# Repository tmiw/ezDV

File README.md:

# ezDV

This repository contains both the hardware and firmware for a portable battery-powered device that can
(de)modulate [FreeDV](https://freedv.org/) from an attached radio. The board is centered around the 
following components:

* [Espressif ESP32-S3](https://www.espressif.com/sites/default/files/documentation/esp32-s3_datasheet_en.pdf)
* [TLV320 digital audio codec chip](https://www.ti.com/cn/lit/ds/symlink/tlv320aic3254.pdf?ts=1651153824042) produced by Texas Instruments ([application notes](https://www.ti.com/lit/an/slaa408a/slaa408a.pdf?ts=1651208477772&ref_url=https%253A%252F%252Fwww.google.com%252F)).

## User's guide

See [here](https://tmiw.github.io/ezDV/) for the latest copy of the user manual for ezDV, which describes its
general use and operation.

## Building the firmware

Install [ESP-IDF v5.3](https://docs.espressif.com/projects/esp-idf/en/v5.3/esp32s3/get-started/index.html) and then run the following:

```
. /path/to/esp-idf/export.sh
git submodule update --init --checkout --recursive
cd firmware
idf.py build
```
## Flashing the firmware

### Using ESP-IDF

Turn on ezDV (see below) and plug it into your computer's USB port, then run the following:

```
idf.py -p /dev/ttyxxx0 flash monitor
```

Where `/dev/ttyxxx0` (or `COMx:` on Windows) is the serial port created by your operating system after plugging ezDV in.

### Using ESP Flash Tool

On Windows, you can use the ESP Flash Tool to flash ezDV. This does not require installation of ESP-IDF.

1. Download the ESP Flash Tool from https://www.espressif.com/en/support/download/other-tools.
2. Decompress all of the files in the ZIP file and execute flash\_download\_tool\_3.9.3.exe.
3. Select "ESP32-S3" for "ChipType", "Develop" for "WorkMode" and "USB" for "LoadMode" as shown below:

4. Add rows for each of the .bin files in the resulting screen:

| File Name | Offset |
|---|---|
| bootloader.bin | 0x0 |
| partition-table.bin | 0x8000 |
| ota\_data\_initial.bin | 0xF000 |
| ezdv.bin | 0x20000 |
| http_0.bin | 0x7F8000 |
| q8_models.bin | 0xAE6000 |

Additionally, check each of the checkboxes to the left of the file name. It should look something like this, with each of the rows having a green background:

5. Set "SPI SPEED" to "80 MHz" and "SPI MODE" to "DIO".

6. Plug ezDV into your computer using a USB-C cable and turn it on by holding down the Mode button for a few seconds. Device Manager should show a new COM port named "USB/JTAG serial debug unit" or similar. Enter this COM port into the "COM" field in the application.

7. (Optional) Push the ERASE button. This will show a green "SYNC" indicator for a bit followed by "Download" and then "FINISH" as per the above screenshot. *Note: There will be no firmware installed on the board once this step finishes. You will need to reconfigure ezDV after new firmware has been flashed.*

8. Push the START button. This will go through the same indicators as step 1 but this time will also have a progress bar indicating how far it's gotten in flashing the new software. 

9. Push the STOP button and then close the application. Open the ezDV enclosure and briefly push/release the "Reset" button on the right hand side of the board. If everything went well, you'll see the four LEDs light up for a few seconds indicating that ezDV is booting normally.

### Using esptool

You can also use [esptool](https://github.com/espressif/esptool). From the folder you decompressed the "-full.tar.gz" file into, run:

```
esptool.py --chip esp32s3 -p /dev/cu.usbmodem14101 -b 460800 --before=default_reset --after=hard_reset write_flash --flash_mode dio --flash_freq 80m --flash_size detect 0x0 bootloader.bin 0x20000 ezdv.bin 0x8000 partition-table.bin 0xf000 ota_data_initial.bin 0x7f8000 http_0.bin 0xae6000 q8_models.bin
```

### Flashing test firmware

Firmware that hasn't been released yet (for example, from a pull request that needs testing) is built automatically
for every change made to ezDV's source code. To download it:

1. Sign in to GitHub. (Downloads of test firmware are only available to signed-in users.)
2. Go to the [project's Actions page](https://github.com/tmiw/ezDV/actions/workflows/build_ezdv.yml) and select the
   most recent run for the branch you've been asked to test. For a pull request, you can also select the "Build ezDV"
   check at the bottom of the pull request's page and then "Summary".
3. Scroll down to "Artifacts" and download the file named after that branch and commit (for example,
   "ezdv-rade-v2-d8d0042"). This is a ZIP file containing two files ending in "-full.tar.gz" and "-ota.tar.gz".
4. Decompress the "-full.tar.gz" file into a new folder. On Windows, you can do this using 7-Zip or by running
   `tar xzf filename-full.tar.gz` from a Command Prompt.
5. Flash the resulting .bin files using the ESP Flash Tool or esptool as described above.

*Note: Firmware with RADE V2 support adds a "models" area to ezDV's internal memory that holds RADE V2's neural
network. The first time you install it, you must flash all of the files in the "-full.tar.gz" file over USB
as described above. Afterwards, newer test firmware can be installed using the "-ota.tar.gz" file and the web
interface as long as RADE V2's neural network hasn't changed since you last flashed over USB. If in doubt,
flash the "-full.tar.gz" file over USB. Test firmware is not guaranteed to work, so make sure you
can flash ezDV over USB before trying it.*

*To go back to a released version of the firmware, flash that version's "-full.tar.gz" file over USB.*

### Recovering from a bad flash

If the flash process fails (or you are flashing for the first time), you can manually place ezDV into flash mode by holding down the "GPIO0/Flash" button while pushing the "Reset" button on the board. Hold "GPIO0/Flash" for a second or so after releasing Reset, then release. You can then use ESP-IDF, the ESP Flash Tool or esptool to flash ezDV with working firmware.

## Contributing to ezDV

Pleae read the [Theory of Operation](https://github.com/tmiw/ezDV/blob/main/THEORY_OF_OPERATIONS.md) document for more information about the general hardware and software architecture, along with information about how to contribute changes to ezDV.

## License

This project is subject to the terms of the [TAPR Open Hardware License v1.0](https://tapr.org/the-tapr-open-hardware-license/) (schematics, 
other hardware documentation) and [GNU General Public License v3.0](https://www.gnu.org/licenses/gpl-3.0.en.html) (firmware).

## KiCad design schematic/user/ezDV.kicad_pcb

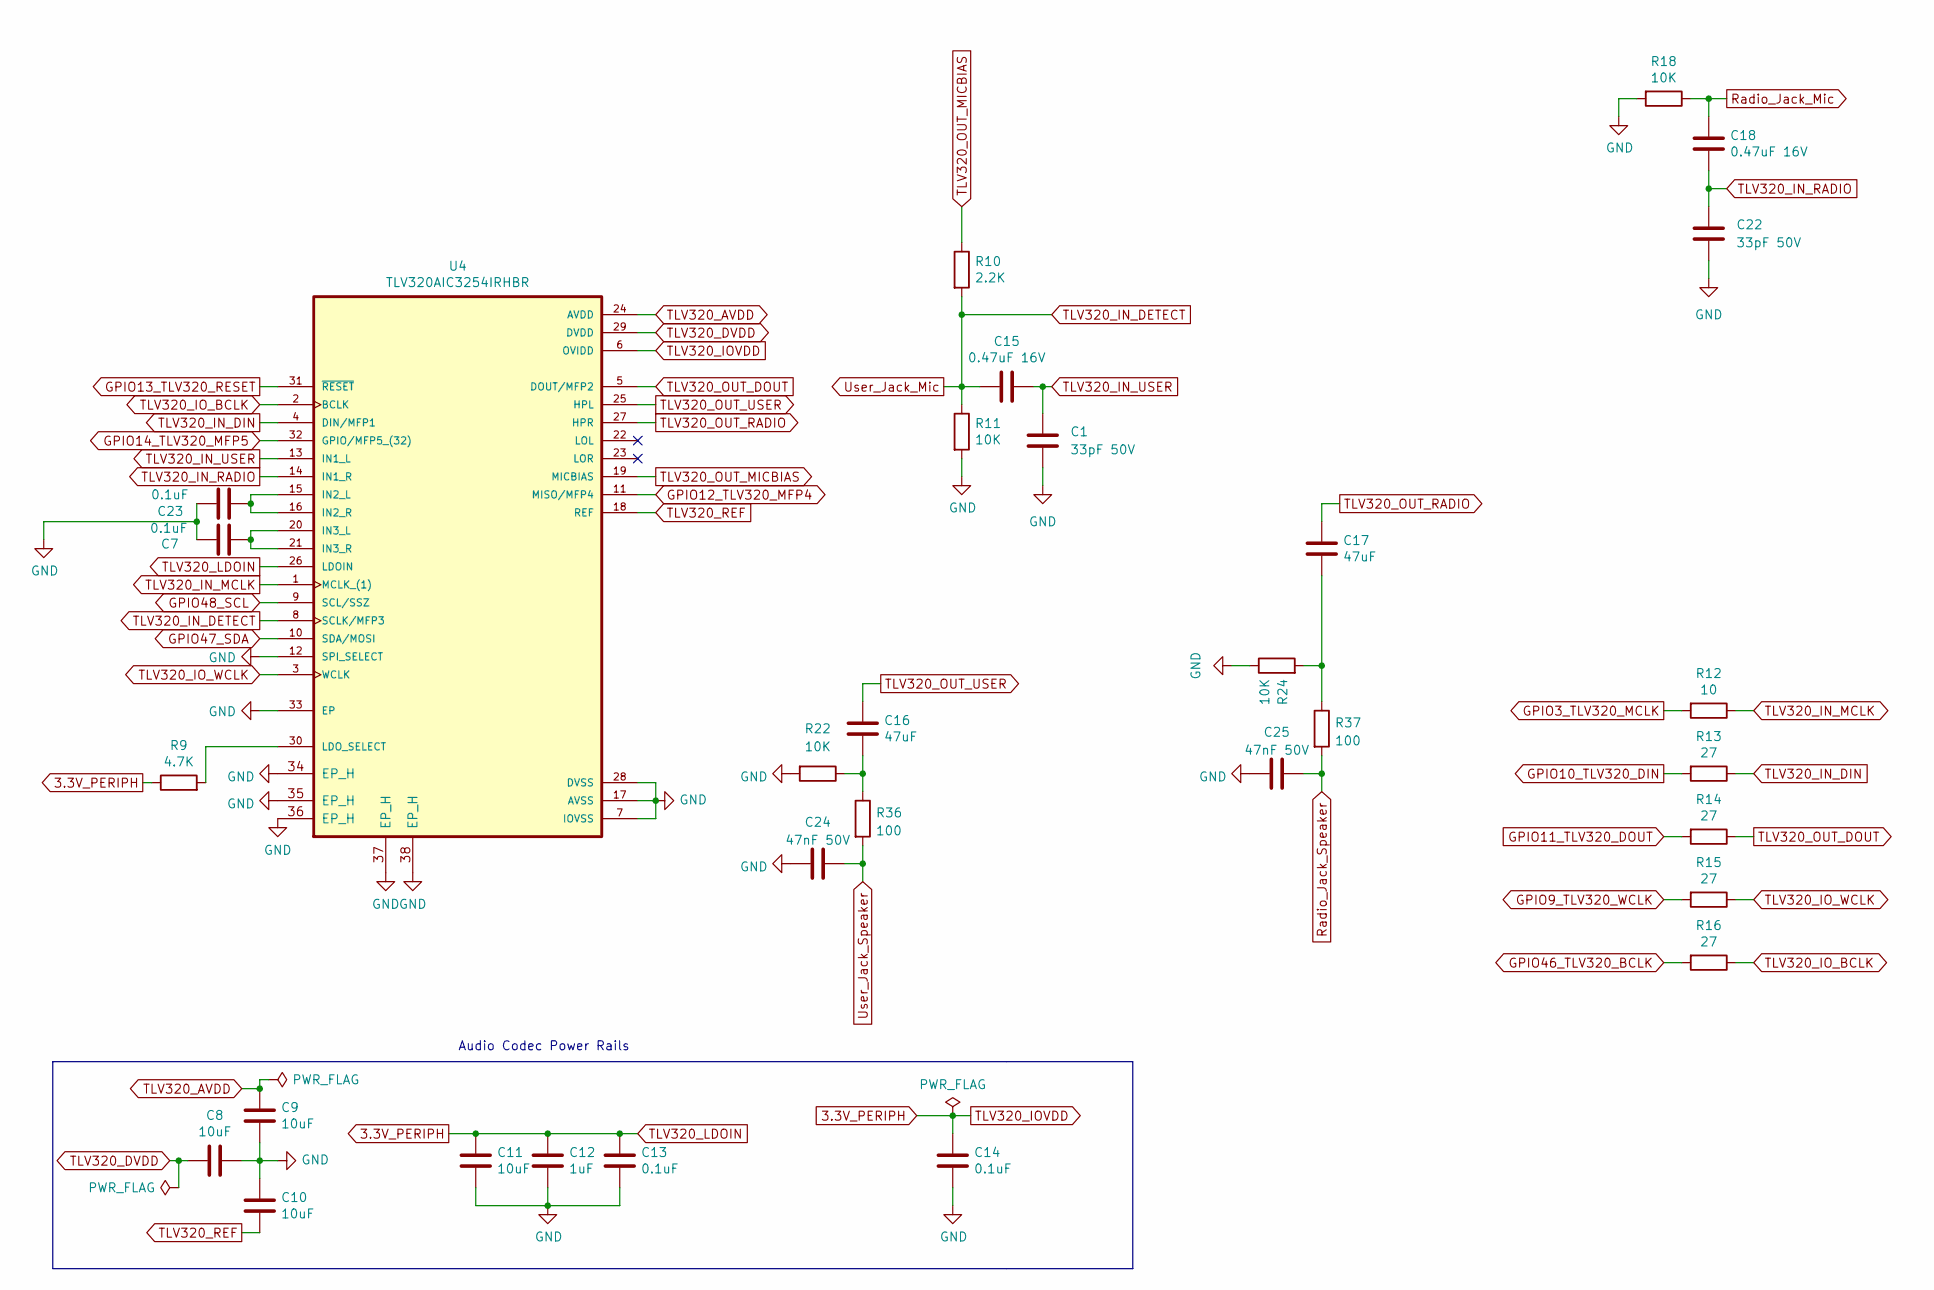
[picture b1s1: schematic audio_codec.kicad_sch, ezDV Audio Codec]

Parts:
C1, C22: 33pF 50V; C_0402_1005Metric; LCSC C1562
C7, C13, C14, C23: 0.1uF; C_0402_1005Metric; LCSC C1525
C8, C9, C10, C11: 10uF; C_0402_1005Metric; LCSC C315248
C12: 1uF; C_0402_1005Metric; LCSC C14445
C15, C18: 0.47uF 16V; C_0402_1005Metric; LCSC C575468
C16, C17: 47uF; C_0603_1608Metric; LCSC C140782
C24, C25: 47nF 50V; C_0402_1005Metric; LCSC C697422
R9: 4.7K; R_0402_1005Metric; LCSC C25900
R10: 2.2K; R_0402_1005Metric; LCSC C114762
R11, R18, R22, R24: 10K; R_0402_1005Metric; LCSC C25744
R12: 10; R_0402_1005Metric; LCSC C25077
R13, R14, R15, R16: 27; R_0402_1005Metric; LCSC C31439
R36, R37: 100; R_0402_1005Metric; LCSC C25076
U4: TLV320AIC3254IRHBR; IC_ADS125H01IRHBT; LCSC C9925

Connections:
3.3V_PERIPH: C11.1, C12.1, C13.1, C14.1, R9.1, U4.6 (OVIDD), U4.26 (LDOIN); also elsewhere on the board
GND: C1.2, C7.2, C8.1, C9.2, C10.1, C11.2, C12.2, C13.2, C14.2, C22.2, C23.2, C24.1, C25.1, R11.2, R18.2, R22.2, R24.1, U4.7 (IOVSS), U4.12 (SPI_SELECT), U4.17 (AVSS), U4.28 (DVSS), U4.33 (EP), U4.34 (EP_H), U4.35 (EP_H), U4.36 (EP_H), U4.37 (EP_H), U4.38 (EP_H); also elsewhere on the board
GPIO3_TLV320_MCLK: R12.2; also elsewhere on the board
GPIO9_TLV320_WCLK: R15.2; also elsewhere on the board
GPIO10_TLV320_DIN: R13.2; also elsewhere on the board
GPIO11_TLV320_DOUT: R14.2; also elsewhere on the board
GPIO12_TLV320_MFP4: U4.11 (MISO/MFP4); also elsewhere on the board
GPIO13_TLV320_RESET: U4.31 (~RESET); also elsewhere on the board
GPIO14_TLV320_MFP5: U4.32 (GPIO/MFP5_(32)); also elsewhere on the board
GPIO46_TLV320_BCLK: R16.2; also elsewhere on the board
GPIO47_SDA: U4.10 (SDA/MOSI); also elsewhere on the board
GPIO48_SCL: U4.9 (SCL/SSZ); also elsewhere on the board
unnamed: C7.1, U4.15 (IN2_L), U4.16 (IN2_R)
unnamed: C16.2, R22.1, R36.1
unnamed: C17.2, R24.2, R37.1
unnamed: C23.1, U4.20 (IN3_L), U4.21 (IN3_R)
unnamed: R9.2, U4.30 (LDO_SELECT)
Radio_Jack_Mic: C18.1, R18.1; also elsewhere on the board
Radio_Jack_Speaker: C25.2, R37.2; also elsewhere on the board
TLV320_AVDD: C9.1, U4.24 (AVDD)
TLV320_DVDD: C8.2, U4.29 (DVDD)
TLV320_IN_DETECT: C15.1, R10.2, R11.1, U4.8 (SCLK/MFP3); also elsewhere on the board
TLV320_IN_DIN: R13.1, U4.4 (DIN/MFP1)
TLV320_IN_MCLK: R12.1, U4.1 (MCLK_(1))
TLV320_IN_RADIO: C18.2, C22.1, U4.14 (IN1_R)
TLV320_IN_USER: C1.1, C15.2, U4.13 (IN1_L)
TLV320_IO_BCLK: R16.1, U4.2 (BCLK)
TLV320_IO_WCLK: R15.1, U4.3 (WCLK)
TLV320_OUT_DOUT: R14.1, U4.5 (DOUT/MFP2)
TLV320_OUT_MICBIAS: R10.1, U4.19 (MICBIAS)
TLV320_OUT_RADIO: C17.1, U4.27 (HPR)
TLV320_OUT_USER: C16.1, U4.25 (HPL)
TLV320_REF: C10.2, U4.18 (REF)
User_Jack_Speaker: C24.2, R36.2; also elsewhere on the board

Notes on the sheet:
Audio Codec Power Rails

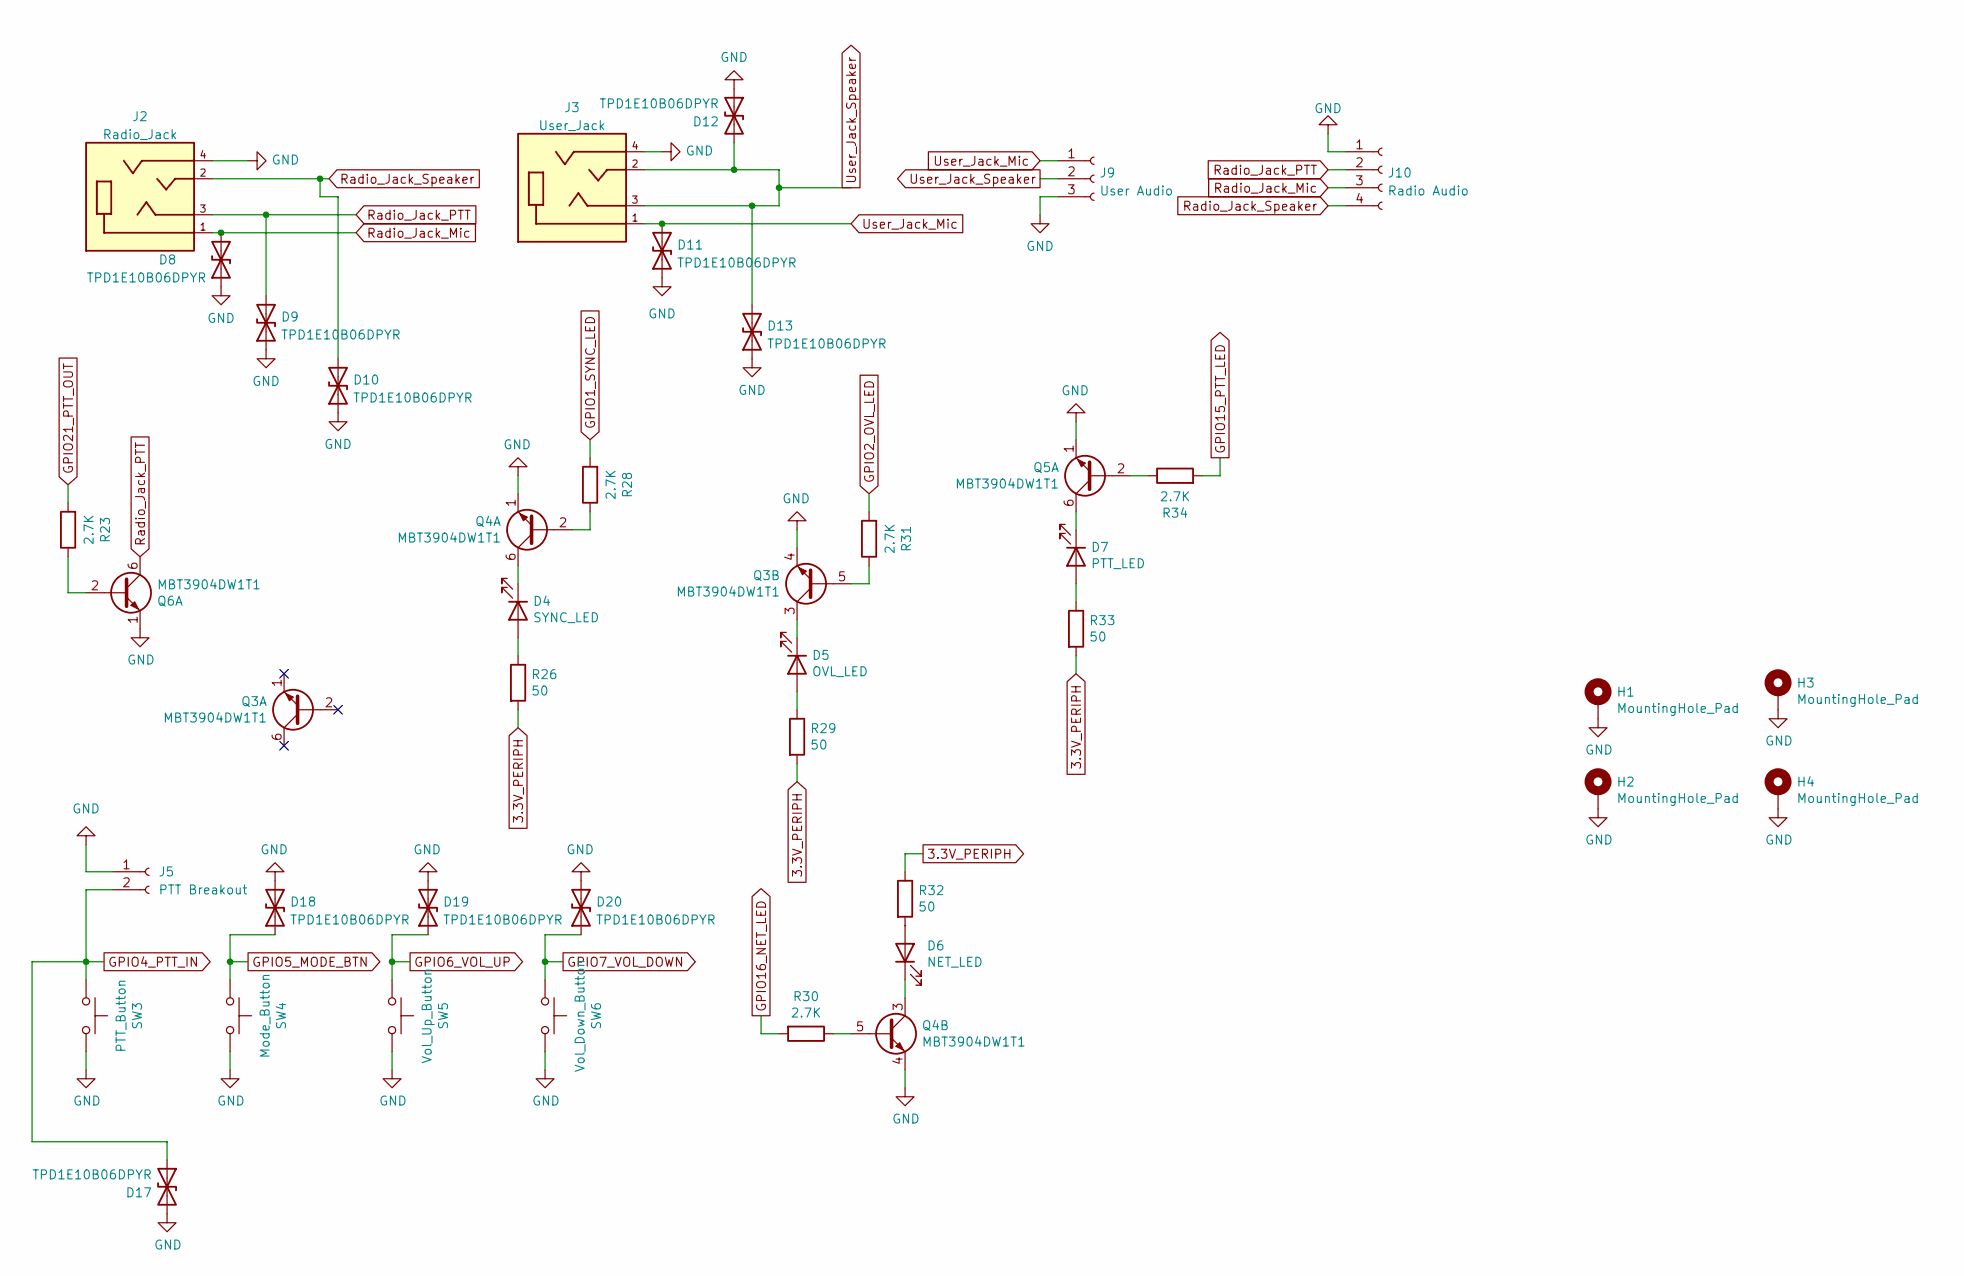
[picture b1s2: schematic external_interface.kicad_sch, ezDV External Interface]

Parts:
D4: SYNC_LED; D_0603_1608Metric; LCSC C434423
D5: OVL_LED; D_0603_1608Metric; LCSC C2286
D6: NET_LED; D_0603_1608Metric; LCSC C72041
D7: PTT_LED; D_0603_1608Metric; LCSC C2286
D8, D9, D10, D11, D12, D13, D17, D18, D19, D20: TPD1E10B06DPYR; DIO_TPD1E05U06DPYR; LCSC C48260
H1, H2, H3, H4: MountingHole_Pad; MountingHole_3.2mm_M3_Pad
J2: Radio_Jack; CUI_SJ-43514; PART_REV 1.04
J3: User_Jack; CUI_SJ-43514; PART_REV 1.04
J5: PTT Breakout; PinHeader_1x02_P2.54mm_Vertical
J9: User Audio; PinSocket_1x03_P2.54mm_Vertical
J10: Radio Audio; PinHeader_1x04_P2.54mm_Vertical
Q3, Q4, Q5, Q6: MBT3904DW1T1; SOT-363_SC-70-6; LCSC C110150
R23, R28, R30, R31, R34: 2.7K; R_0603_1608Metric; LCSC C13167
R26, R29, R32, R33: 50; R_0603_1608Metric; LCSC C22808
SW3: PTT_Button; SW_SPST_TL3305C; LCSC C2886904
SW4: Mode_Button; SW_SPST_TL3305C; LCSC C2886904
SW5: Vol_Up_Button; SW_SPST_TL3305C; LCSC C2886904
SW6: Vol_Down_Button; SW_SPST_TL3305C; LCSC C2886904

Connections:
3.3V_PERIPH: R26.2, R29.2, R32.1, R33.2; also elsewhere on the board
GND: D8.1 (A1), D9.1 (A1), D10.1 (A1), D11.1 (A1), D12.1 (A1), D13.1 (A1), D17.2 (A2), D18.2 (A2), D19.2 (A2), D20.2 (A2), H1.1, H2.1, H3.1, H4.1, J2.4, J3.4, J5.1, J9.3, J10.1, Q3.4 (E2), Q4.1 (E1), Q4.4 (E2), Q5.1 (E1), Q6.1 (E1), SW3.2, SW4.2, SW5.2, SW6.2; also elsewhere on the board
GPIO1_SYNC_LED: R28.2; also elsewhere on the board
GPIO2_OVL_LED: R31.2; also elsewhere on the board
GPIO4_PTT_IN: D17.1 (A1), J5.2, SW3.1; also elsewhere on the board
GPIO5_MODE_BTN: D18.1 (A1), SW4.1; also elsewhere on the board
GPIO6_VOL_UP: D19.1 (A1), SW5.1; also elsewhere on the board
GPIO7_VOL_DOWN: D20.1 (A1), SW6.1; also elsewhere on the board
GPIO15_PTT_LED: R34.2; also elsewhere on the board
GPIO16_NET_LED: R30.2; also elsewhere on the board
GPIO21_PTT_OUT: R23.2; also elsewhere on the board
unnamed: D4.1 (K), Q4.6 (C1)
unnamed: D4.2 (A), R26.1
unnamed: D5.1 (K), Q3.3 (C2)
unnamed: D5.2 (A), R29.1
unnamed: D6.1 (K), Q4.3 (C2)
unnamed: D6.2 (A), R32.2
unnamed: D7.1 (K), Q5.6 (C1)
unnamed: D7.2 (A), R33.1
unnamed: Q3.5 (B2), R31.1
unnamed: Q4.2 (B1), R28.1
unnamed: Q4.5 (B2), R30.1
unnamed: Q5.2 (B1), R34.1
unnamed: Q6.2 (B1), R23.1
Radio_Jack_Mic: D8.2 (A2), J2.1, J10.3; also elsewhere on the board
Radio_Jack_PTT: D9.2 (A2), J2.3, J10.2, Q6.6 (C1)
Radio_Jack_Speaker: D10.2 (A2), J2.2, J10.4; also elsewhere on the board
TLV320_IN_DETECT: D11.2 (A2), J3.1, J9.1; also elsewhere on the board
User_Jack_Speaker: D12.2 (A2), D13.2 (A2), J3.2, J3.3, J9.2; also elsewhere on the board

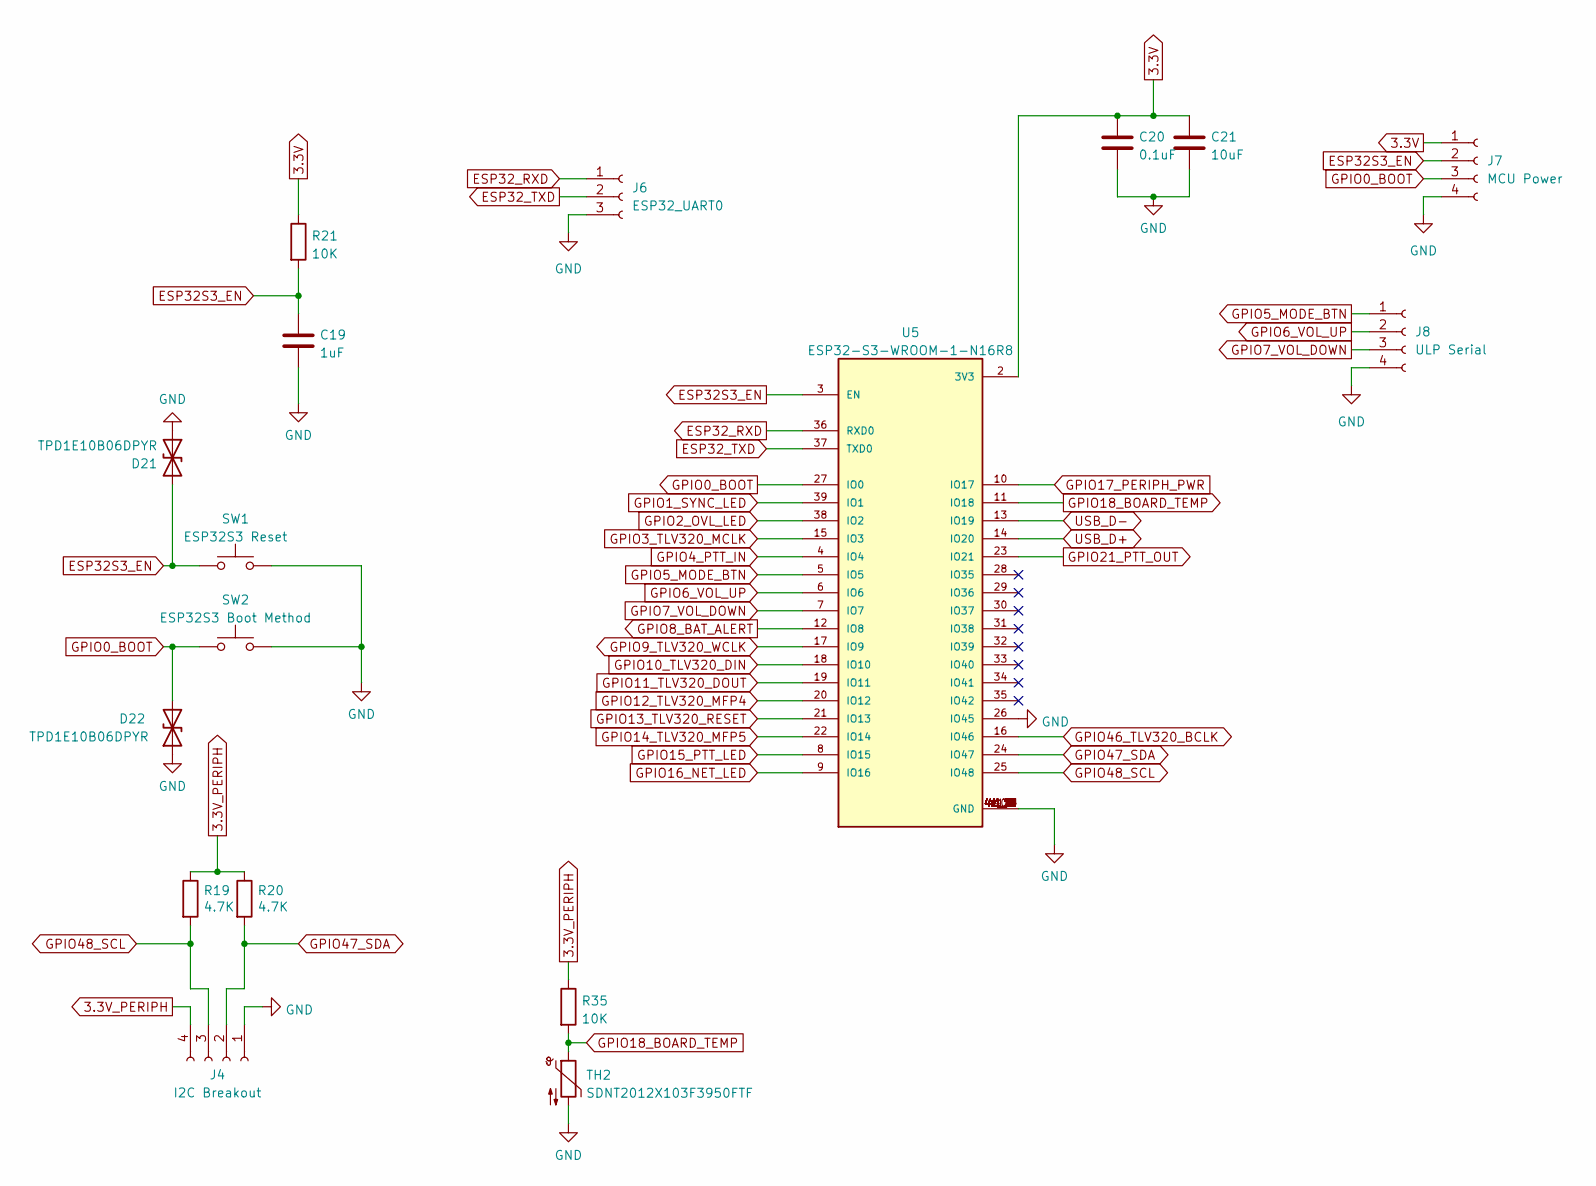
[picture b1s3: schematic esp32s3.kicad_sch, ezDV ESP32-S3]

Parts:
C19: 1uF; C_0402_1005Metric; LCSC C14445
C20: 0.1uF; C_0402_1005Metric; LCSC C1525
C21: 10uF; C_0402_1005Metric; LCSC C315248
D21, D22: TPD1E10B06DPYR; DIO_TPD1E05U06DPYR; LCSC C48260
J4: I2C Breakout; PinHeader_1x04_P2.54mm_Vertical
J6: ESP32_UART0; PinHeader_1x03_P2.54mm_Vertical
J7: MCU Power; PinHeader_1x04_P2.54mm_Vertical
J8: ULP Serial; PinHeader_2x02_P2.54mm_Vertical
R19, R20: 4.7K; R_0603_1608Metric; LCSC C99782
R21, R35: 10K; R_0402_1005Metric; LCSC C25744
SW1: ESP32S3 Reset; SW_SPST_TL3342; LCSC C2886898
SW2: ESP32S3 Boot Method; SW_SPST_TL3342; LCSC C2886898
TH2: SDNT2012X103F3950FTF; R_0805_2012Metric; LCSC C95968
U5: ESP32-S3-WROOM-1-N16R8; XCVR_ESP32S3WROOM1N8R8; LCSC C2913202

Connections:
3.3V: C20.1, C21.1, J7.1, R21.1, U5.2 (3V3); also elsewhere on the board
3.3V_PERIPH: J4.4, R19.1, R20.1, R35.1; also elsewhere on the board
ESP32S3_EN: C19.1, D21.2 (A2), J7.2, R21.2, SW1.1, U5.3 (EN)
ESP32_RXD: J6.1, U5.36 (RXD0)
ESP32_TXD: J6.2, U5.37 (TXD0)
GND: C19.2, C20.2, C21.2, D21.1 (A1), D22.1 (A1), J4.1, J6.3, J7.4, J8.4, SW1.2, SW2.2, TH2.2, U5.1 (GND), U5.26 (IO45), U5.40 (GND), U5.41_1 (GND), U5.41_2 (GND), U5.41_3 (GND), U5.41_4 (GND), U5.41_5 (GND), U5.41_6 (GND), U5.41_7 (GND), U5.41_8 (GND), U5.41_9 (GND), U5.41_10 (GND), U5.41_11 (GND), U5.41_12 (GND), U5.41_13 (GND), U5.41_14 (GND), U5.41_15 (GND), U5.41_16 (GND), U5.41_17 (GND), U5.41_18 (GND), U5.41_19 (GND), U5.41_20 (GND), U5.41_21 (GND); also elsewhere on the board
GPIO0_BOOT: D22.2 (A2), J7.3, SW2.1, U5.27 (IO0)
GPIO1_SYNC_LED: U5.39 (IO1); also elsewhere on the board
GPIO2_OVL_LED: U5.38 (IO2); also elsewhere on the board
GPIO3_TLV320_MCLK: U5.15 (IO3); also elsewhere on the board
GPIO4_PTT_IN: U5.4 (IO4); also elsewhere on the board
GPIO5_MODE_BTN: J8.1, U5.5 (IO5); also elsewhere on the board
GPIO6_VOL_UP: J8.2, U5.6 (IO6); also elsewhere on the board
GPIO7_VOL_DOWN: J8.3, U5.7 (IO7); also elsewhere on the board
GPIO8_BAT_ALERT: U5.12 (IO8); also elsewhere on the board
GPIO9_TLV320_WCLK: U5.17 (IO9); also elsewhere on the board
GPIO10_TLV320_DIN: U5.18 (IO10); also elsewhere on the board
GPIO11_TLV320_DOUT: U5.19 (IO11); also elsewhere on the board
GPIO12_TLV320_MFP4: U5.20 (IO12); also elsewhere on the board
GPIO13_TLV320_RESET: U5.21 (IO13); also elsewhere on the board
GPIO14_TLV320_MFP5: U5.22 (IO14); also elsewhere on the board
GPIO15_PTT_LED: U5.8 (IO15); also elsewhere on the board
GPIO16_NET_LED: U5.9 (IO16); also elsewhere on the board
GPIO17_PERIPH_PWR: U5.10 (IO17); also elsewhere on the board
GPIO18_BOARD_TEMP: R35.2, TH2.1, U5.11 (IO18)
GPIO21_PTT_OUT: U5.23 (IO21); also elsewhere on the board
GPIO46_TLV320_BCLK: U5.16 (IO46); also elsewhere on the board
GPIO47_SDA: J4.2, R20.2, U5.24 (IO47); also elsewhere on the board
GPIO48_SCL: J4.3, R19.2, U5.25 (IO48); also elsewhere on the board
USB_D+: U5.14 (IO20); also elsewhere on the board
USB_D-: U5.13 (IO19); also elsewhere on the board

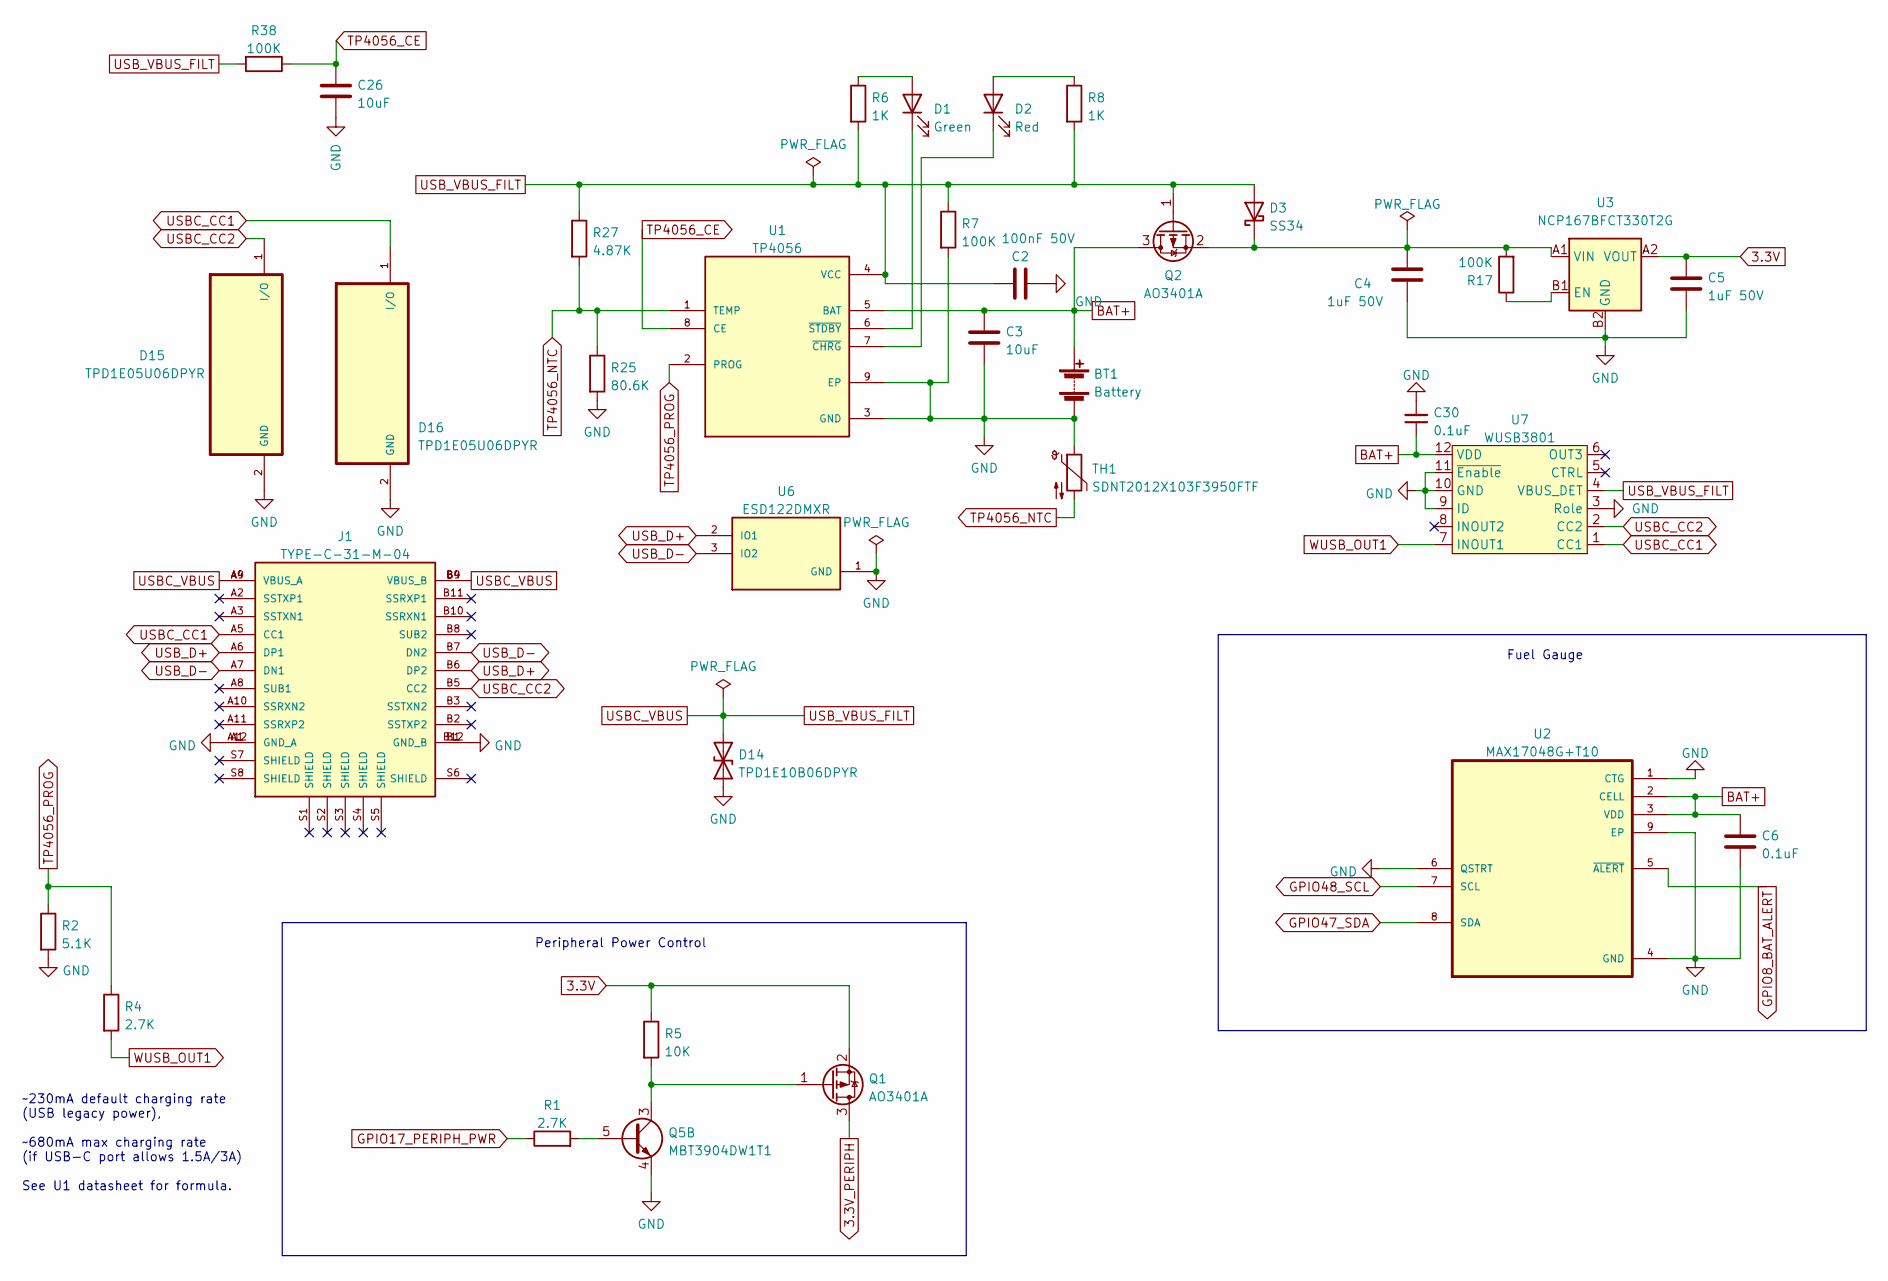
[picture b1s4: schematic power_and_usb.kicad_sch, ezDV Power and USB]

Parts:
BT1: Battery; PinSocket_1x02_P2.54mm_Vertical
C2: 100nF 50V; C_0402_1005Metric; LCSC C307331
C3: 10uF; C_0402_1005Metric; LCSC C315248
C4, C5: 1uF 50V; C_0805_2012Metric; LCSC C28323
C6, C30: 0.1uF; C_0402_1005Metric; LCSC C1525
C26: 10uF; C_0402_1005Metric; LCSC C307415
D1: Green; D_0603_1608Metric; LCSC C434423
D2: Red; D_0603_1608Metric; LCSC C2286
D3: SS34; D_SMA; LCSC C8678
D14: TPD1E10B06DPYR; DIO_TPD1E05U06DPYR; LCSC C48260
D15, D16: TPD1E05U06DPYR; DIO_TPD1E05U06DPYR; LCSC C436349
J1: TYPE-C-31-M-04; HRO_TYPE-C-31-M-04; PARTREV A; LCSC C129018
Q1, Q2: AO3401A; SOT-23; LCSC C15127
Q5: MBT3904DW1T1; SOT-363_SC-70-6; LCSC C110150
R1: 2.7K; R_0603_1608Metric; LCSC C13167
R2: 5.1K; R_0402_1005Metric; LCSC C25905
R4: 2.7K; R_0402_1005Metric; LCSC C138017
R5: 10K; R_0402_1005Metric; LCSC C25744
R6, R8: 1K; R_0402_1005Metric; LCSC C85373
R7, R17, R38: 100K; R_0402_1005Metric; LCSC C25741
R25: 80.6K; R_0603_1608Metric; LCSC C403361
R27: 4.87K; R_0805_2012Metric; LCSC C218605
TH1: SDNT2012X103F3950FTF; R_0805_2012Metric; LCSC C95968
U1: TP4056; SOP127P600X175-9N; LCSC C16581
U2: MAX17048G+T10; SON50P200X200X80-9N; LCSC C2682616
U3: NCP167BFCT330T2G; BGA4N35P2X2_64X64X33N; LCSC C603663
U6: ESD122DMXR; IC_ESD122DMXR; PARTREV A; LCSC C544474
U7: WUSB3801; QFN1616-12L; LCSC C2931342

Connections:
3.3V: C5.1, Q1.2 (S), R5.1, U3.A2 (VOUT); also elsewhere on the board
3.3V_PERIPH: Q1.3 (D); also elsewhere on the board
BAT+: BT1.1 (+), C3.1, C6.1, C30.1, Q2.3 (D), U1.5 (BAT), U2.2 (CELL), U2.3 (VDD), U7.12 (VDD)
GND: BT1.2 (-), C2.1, C3.2, C4.2, C5.2, C6.2, C26.1, C30.2, D14.1 (A1), D15.2 (GND), D16.2 (GND), J1.A1 (GND_A), J1.A12 (GND_A), J1.B1 (GND_B), J1.B12 (GND_B), Q5.4 (E2), R2.2, R7.2, R25.2, TH1.1, U1.3 (GND), U1.9 (EP), U2.1 (CTG), U2.4 (GND), U2.6 (QSTRT), U2.9 (EP), U3.B2 (GND), U6.1 (GND), U7.3 (Role), U7.9 (ID), U7.10 (GND), U7.11 (~Enable); also elsewhere on the board
GPIO8_BAT_ALERT: U2.5 (~ALERT); also elsewhere on the board
GPIO17_PERIPH_PWR: R1.1; also elsewhere on the board
GPIO47_SDA: U2.8 (SDA); also elsewhere on the board
GPIO48_SCL: U2.7 (SCL); also elsewhere on the board
unnamed: C4.1, D3.1 (K), Q2.2 (S), R17.2, U3.A1 (VIN)
unnamed: D1.1 (K), U1.6 (~STDBY)
unnamed: D1.2 (A), R6.1
unnamed: D2.1 (K), U1.7 (~CHRG)
unnamed: D2.2 (A), R8.1
unnamed: Q1.1 (G), Q5.3 (C2), R5.2
unnamed: Q5.5 (B2), R1.2
unnamed: R17.1, U3.B1 (EN)
TP4056_CE: C26.2, R38.1, U1.8 (CE)
TP4056_NTC: R25.1, R27.2, TH1.2, U1.1 (TEMP)
TP4056_PROG: R2.1, R4.1, U1.2 (PROG)
USBC_CC1: D16.1 (I/O), J1.A5 (CC1), U7.1 (CC1)
USBC_CC2: D15.1 (I/O), J1.B5 (CC2), U7.2 (CC2)
USB_D+: J1.A6 (DP1), J1.B6 (DP2), U6.2 (IO1); also elsewhere on the board
USB_D-: J1.A7 (DN1), J1.B7 (DN2), U6.3 (IO2); also elsewhere on the board
WUSB_OUT1: R4.2, U7.7 (INOUT1)

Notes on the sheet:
Fuel Gauge
Peripheral Power Control
~230mA default charging rate (USB legacy power), ~680mA max charging rate (if USB-C port allows 1.5A/3A) See U1 datasheet for formula.

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
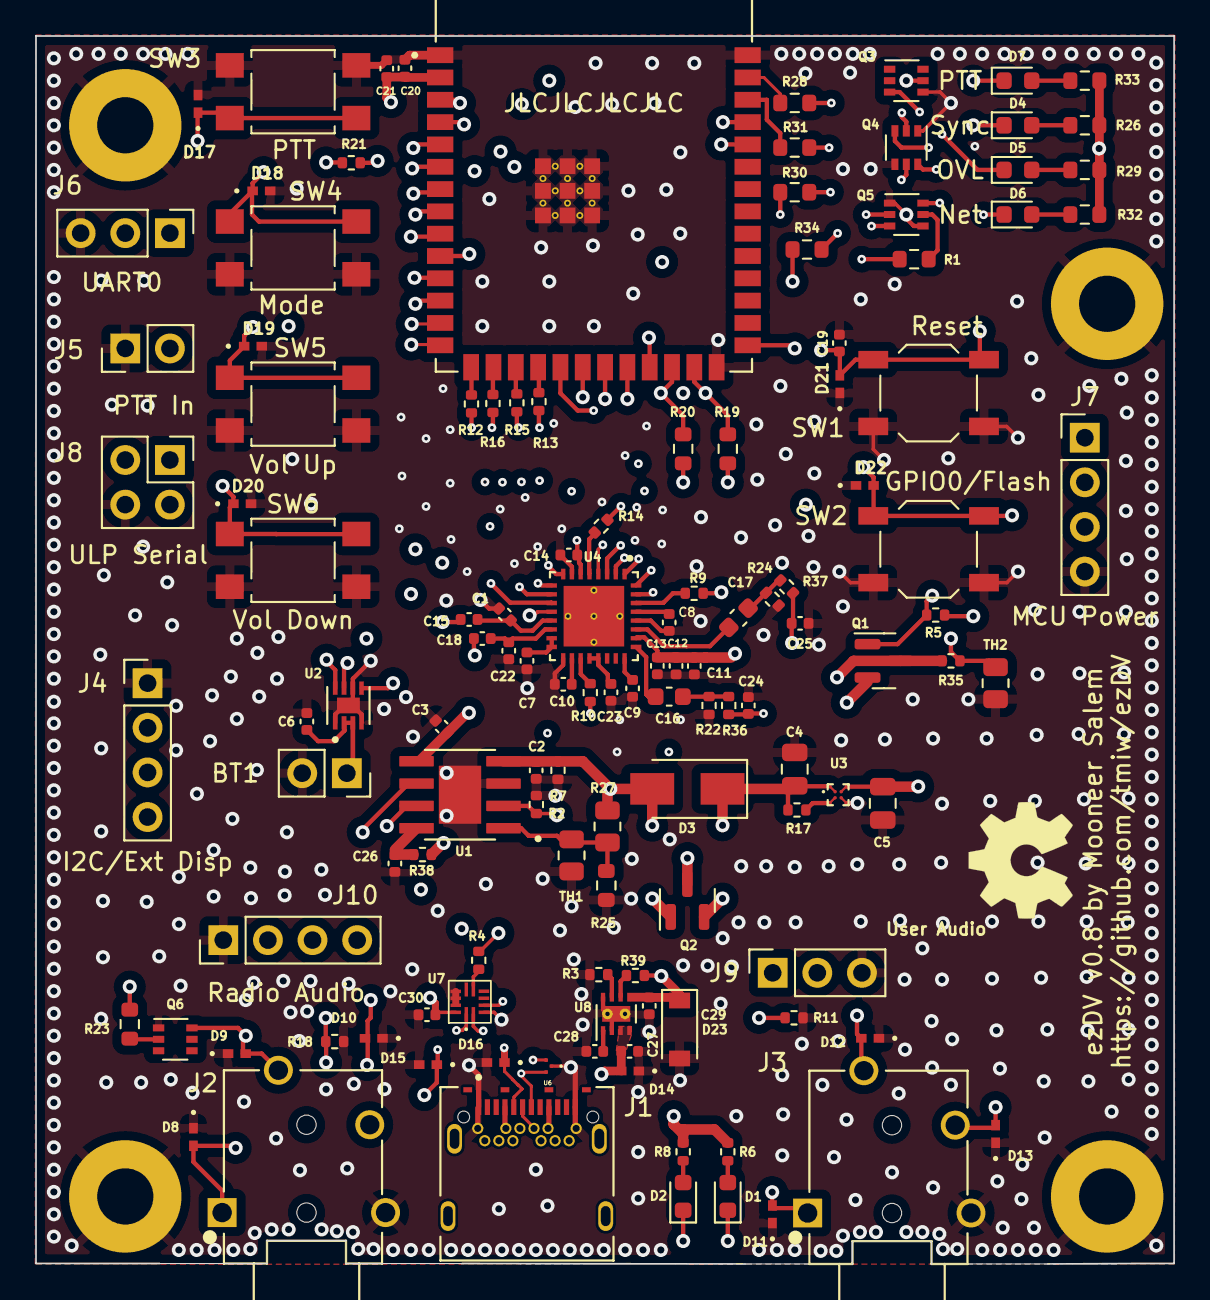
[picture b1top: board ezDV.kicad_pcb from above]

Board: 6 copper layers, 64.8 x 69.9 mm, 129 parts (0 on the bottom side), 87 nets.

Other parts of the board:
C27: 0.1uF; C_0402_1005Metric
C28: 8.2nF; C_0402_1005Metric
C29: 10uF; C_0402_1005Metric
D23: B5819W SL; D_SOD-123
R3: 1300; R_0402_1005Metric
R39: 100K; R_0402_1005Metric
U8: TPS259533; WSON-8-1EP_2x2mm_P0.5mm_EP0.9x1.6mm_ThermalVias

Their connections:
GND: C27.1, C28.2, C29.2, D23.2 (A), R3.2, U8.2 (~EN), U8.8 (GND), U8.9 (PAD); also elsewhere on the board
unnamed: C28.1, U8.1 (dV/dT)
unnamed: R3.1, U8.7 (ILM)
unnamed: R39.2, U8.6 (~FLT)
